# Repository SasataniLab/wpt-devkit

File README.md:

# wpt-devkit-v0.1 SCPI Command Set
Hardware tool and Arduino library for developing wireless power applications.

## Command reference
[SCPI command reference](./docs/SCPI.md)

## Arduino IDE
### Installation
Add `wpt-io-arduino.zip` in release.
- Sketch -> Include Library -> Add .ZIP Library

### Dependencies
**Manual ZIP install**
- [bschulz1701/PAC1720_Library](https://github.com/bschulz1701/PAC1720_Library)

**Arduino Library Manager**
- [WifWaf/MCP45HVX1](https://github.com/WifWaf/MCP45HVX1)

### Update
You need to manually uninstall to update. We plan to add this to Arduino Library Manager to automate this in the future.

## Examples
See [Examples](./firmware/wpt-io-arduino/examples) for example Arduino sketches

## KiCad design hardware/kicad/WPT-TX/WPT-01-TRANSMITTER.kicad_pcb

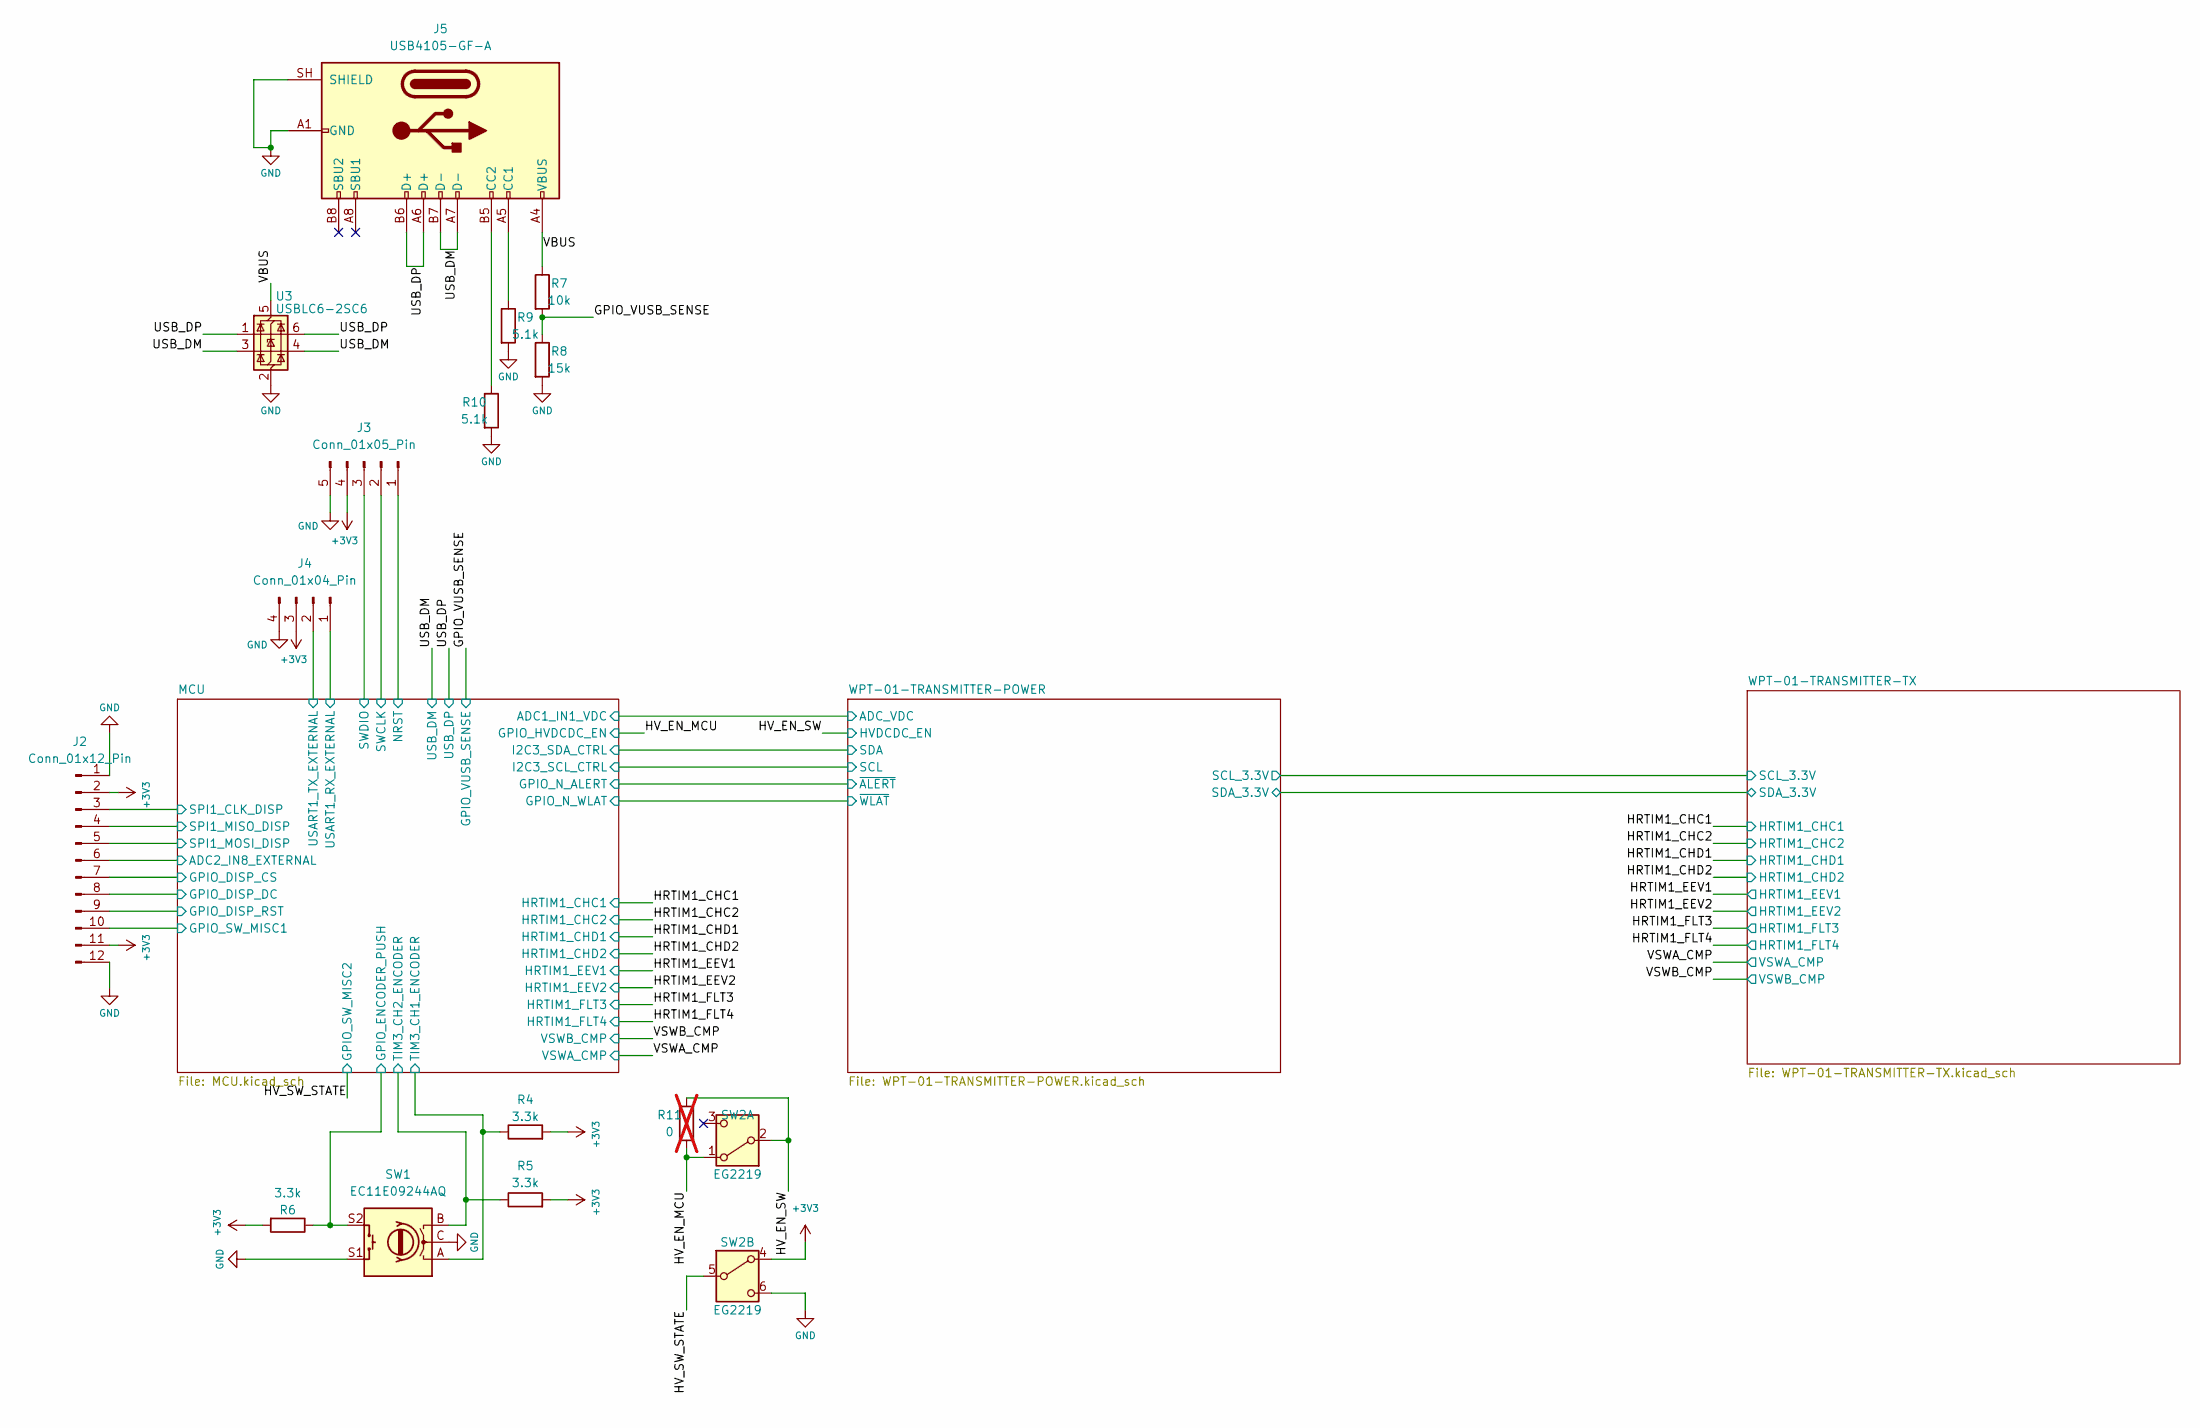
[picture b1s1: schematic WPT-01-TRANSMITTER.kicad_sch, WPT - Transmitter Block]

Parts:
J2: Conn_01x12_Pin; PinHeader_1x12_P2.54mm_Vertical
J3: Conn_01x05_Pin; PinHeader_1x05_P2.54mm_Vertical
J4: Conn_01x04_Pin; PinHeader_1x04_P2.54mm_Vertical
J5: USB4105-GF-A; USB_C_Receptacle_GCT_USB4105-xx-A_16P_TopMnt_Horizontal
R4, R5, R6: 3.3k; R_0402_1005Metric
R7: 10k; R_0402_1005Metric
R8: 15k; R_0402_1005Metric
R9, R10: 5.1k; R_0402_1005Metric
R11: 0; R_0402_1005Metric; not fitted
SW1: EC11E09244AQ; RotaryEncoder_Alps_EC11E-Switch_Vertical_H20mm
SW2: EG2219; SW_E-Switch_EG2219_DPDT_Angled
U3: USBLC6-2SC6; SOT-23-6

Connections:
+3V3: J2.2, J2.11, J3.4, J4.3, R4.2, R5.2, R6.2, SW2.4 (A); also elsewhere on the board
/GPIO_VUSB_SENSE: R7.2, R8.1; also elsewhere on the board
/HV_EN_MCU: R11.2, SW2.1 (A); also elsewhere on the board
/HV_EN_SW: R11.1, SW2.2 (B); also elsewhere on the board
/HV_SW_STATE: SW2.5 (B); also elsewhere on the board
/MCU/ADC2_IN8_EXTERNAL: J2.6; also elsewhere on the board
/MCU/GPIO_DISP_CS: J2.7; also elsewhere on the board
/MCU/GPIO_DISP_DC: J2.8; also elsewhere on the board
/MCU/GPIO_DISP_RST: J2.9; also elsewhere on the board
/MCU/GPIO_ENCODER_PUSH: R6.1, SW1.S2; also elsewhere on the board
/MCU/GPIO_SW_MISC1: J2.10; also elsewhere on the board
/MCU/NRST: J3.1; also elsewhere on the board
/MCU/SPI1_CLK_DISP: J2.3; also elsewhere on the board
/MCU/SPI1_MISO_DISP: J2.4; also elsewhere on the board
/MCU/SPI1_MOSI_DISP: J2.5; also elsewhere on the board
/MCU/SWCLK: J3.2; also elsewhere on the board
/MCU/SWDIO: J3.3; also elsewhere on the board
/MCU/TIM3_CH1_ENCODER: R4.1, SW1.A; also elsewhere on the board
/MCU/TIM3_CH2_ENCODER: R5.1, SW1.B; also elsewhere on the board
/MCU/USART1_RX_EXTERNAL: J4.1; also elsewhere on the board
/MCU/USART1_TX_EXTERNAL: J4.2; also elsewhere on the board
/USB_DM: J5.A7 (D-), J5.B7 (D-), U3.3 (I/O2), U3.4 (I/O2); also elsewhere on the board
/USB_DP: J5.A6 (D+), J5.B6 (D+), U3.1 (I/O1), U3.6 (I/O1); also elsewhere on the board
/VBUS: J5.A4 (VBUS), J5.A9 (VBUS), J5.B4 (VBUS), J5.B9 (VBUS), R7.1, U3.5 (VBUS)
GND: J2.1, J2.12, J3.5, J4.4, J5.A1 (GND), J5.A12 (GND), J5.B1 (GND), J5.B12 (GND), J5.SH (SHIELD), R8.2, R9.2, R10.2, SW1.C, SW1.S1, SW2.6 (C), U3.2 (GND); also elsewhere on the board
unnamed: J5.A5 (CC1), R9.1
unnamed: J5.B5 (CC2), R10.1

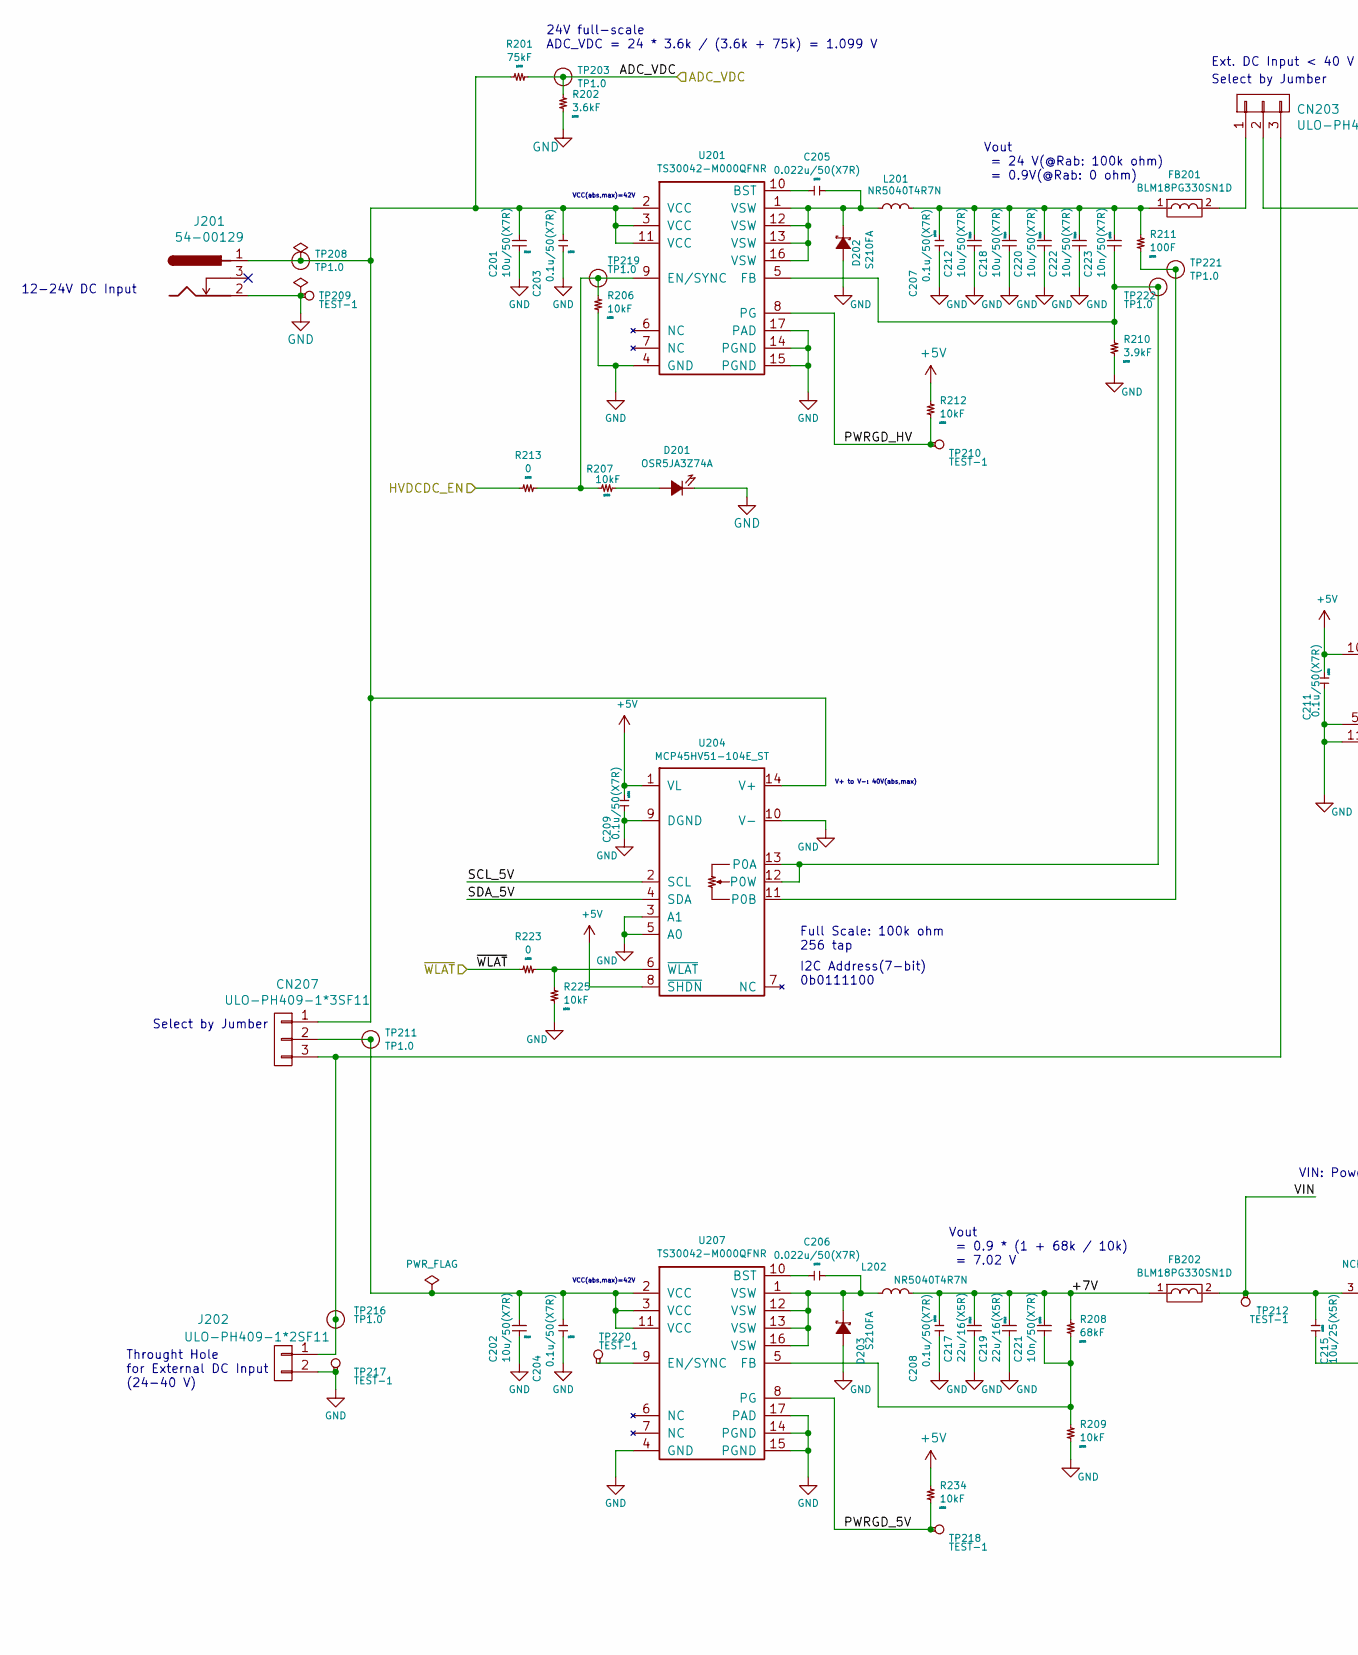
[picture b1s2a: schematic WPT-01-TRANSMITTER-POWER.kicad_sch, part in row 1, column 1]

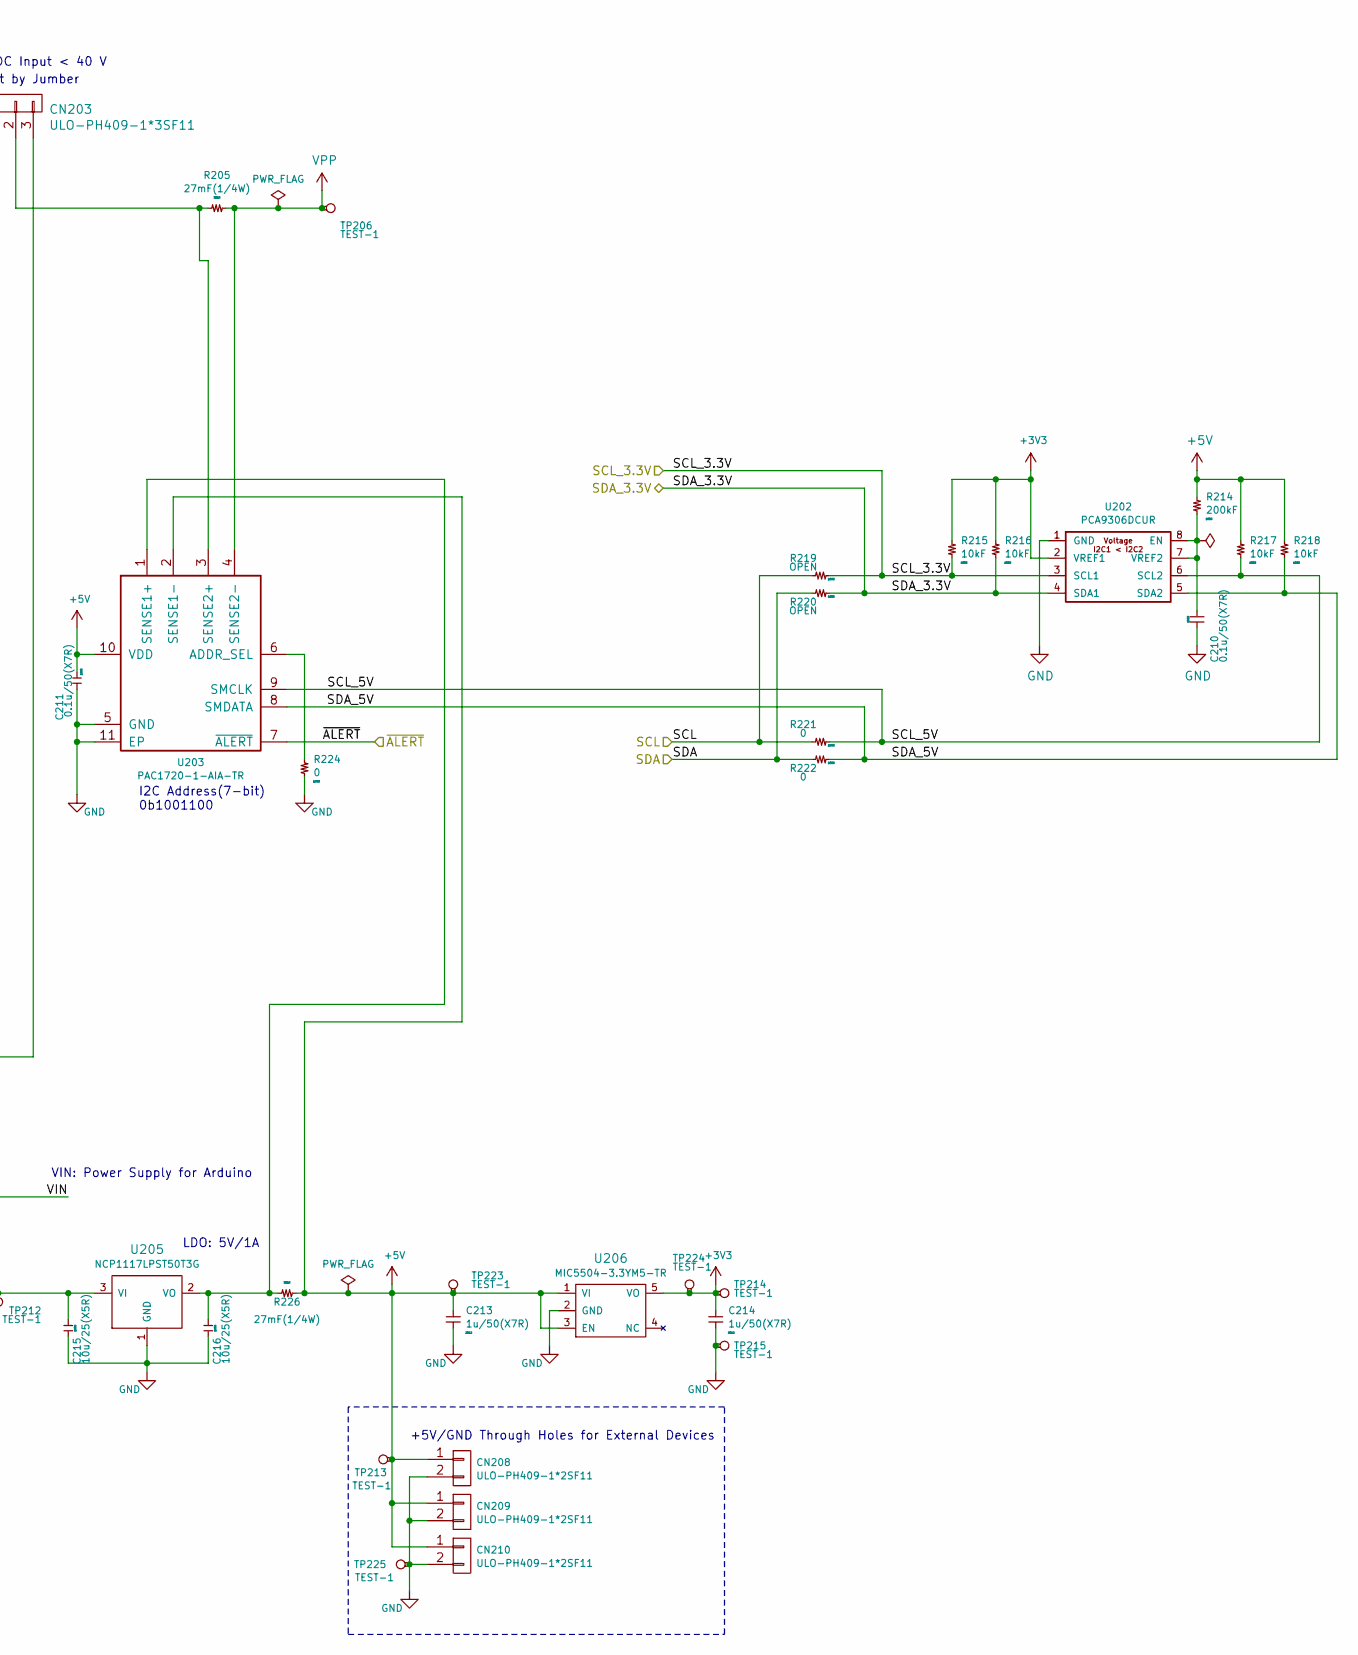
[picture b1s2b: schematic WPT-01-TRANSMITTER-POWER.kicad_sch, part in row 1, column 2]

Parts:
C201, C202, C212, C218, C220, C222: 10u/50(X7R); GRM31; Manufacturer Part Number CL31A106KBHNNNE
C203, C204, C207, C208, C209, C210, C211: 0.1u/50(X7R); GRM15; Manufacturer Part Number GCM155R71H104KE02D
C205, C206: 0.022u/50(X7R); GRM15; Manufacturer Part Number GRM155R71H223KA12D
C213, C214: 1u/50(X7R); GRM21; Manufacturer Part Number CL21B105KBFNNNG
C215, C216: 10u/25(X5R); GRM18; Manufacturer Part Number GRM188R61E106MA73D
C217, C219: 22u/16(X5R); GRM21; Manufacturer Part Number CL21A226MOCLRNC
C221, C223: 10n/50(X7R); GRM15; Manufacturer Part Number CC0402KRX7R9BB103
CN203, CN207: ULO-PH409-1*3SF11; ULO-PH409-1x3SX1; Manufacturer Part Number ULO-PH409-1*3SF11
CN208, CN209, CN210: ULO-PH409-1*2SF11; ULO-PH409-1x2SX1; Manufacturer Part Number ULO-PH409-1x2SX1
D201: OSR5JA3Z74A; LED_D3.0mm; Manufacturer Part Number OSR5JA3Z74A
D202, D203: S210FA; SOD-123FA_OnSemi; Manufacturer Part Number S210FA
FB201, FB202: BLM18PG330SN1D; BLM18; Manufacturer Part Number BLM18PG330SN1D
J201: 54-00129; Manufacturer Part Number 54-00129
J202: ULO-PH409-1*2SF11; ULO-PH409-1x2SX1; Manufacturer Part Number ULO-PH409-1x2SX1
L201: NR5040T4R7N; NR5040
L202: NR5040T4R7N; NR5040; Manufacturer Part Number NR5040T4R7N
R201: 75kF; R_0402; Manufacturer Part Number RC0402FR-0775KL
R202: 3.6kF; R_0402; Manufacturer Part Number RC0402FR-073K6L
R205, R226: 27mF(1/4W); R_1206; Manufacturer Part Number RL1206FR-070R027L
R206, R207, R209, R212, R215, R216, R217, R218, R225, R234: 10kF; R_0402; Manufacturer Part Number RC0402FR-0710KL
R208: 68kF; R_0402; Manufacturer Part Number RC0402FR-0768KL
R210: 3.9kF; R_0402; Manufacturer Part Number RC0402FR-073K9L
R211: 100F; R_0402; Manufacturer Part Number RC0402FR-07100RL
R213, R221, R222, R223, R224: 0; R_0402; Manufacturer Part Number RC0402FR-070RL
R214: 200kF; R_0402; Manufacturer Part Number RC0402FR-07200KL
R219, R220: OPEN; R_0402; Manufacturer Part Number RC0402FR-070RL
TP203, TP208, TP211, TP216, TP219, TP221, TP222: TP1.0; TP_1mm
TP206, TP209, TP210, TP212, TP213, TP214, TP215, TP217, TP218, TP220, TP223, TP224, TP225: TEST-1; PTH_1mm
U201, U207: TS30042-M000QFNR; QFN-16-1EP_3x3mm_Pitch0.5mm_Semtech; Manufacturer Part Number TS30042-M000QFNR
U202: PCA9306DCUR; Texas_S-PDSO-G8; Manufacturer Part Number PCA9306DCUR
U203: PAC1720-1-AIA-TR; DFN-10-1EP_3x3mm_Pitch0.5mm_microchip_9Q; Manufacturer Part Number PAC1720-1-AIA-TR
U204: MCP45HV51-104E_ST; TSSOP-14_4.4x5mm_P0.65mm; Manufacturer Part Number MCP45HV51-104E_ST
U205: NCP1117LPST50T3G; SOT-223-3_TabPin2; Manufacturer Part Number NCP1117LPST50T3G
U206: MIC5504-3.3YM5-TR; microchip_SOT23-5LD-PL-1; Manufacturer Part Number MIC5504-3.3YM5-TR

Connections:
+3V3: C214.1, R215.2, R216.2, TP214.1 (~_1), TP224.1 (~_1), U202.2 (VREF1), U206.5 (VO); also elsewhere on the board
+5V: C209.2, C211.2, C213.1, CN208.1, CN209.1, CN210.1, R212.2, R214.2, R217.2, R218.2, R226.1, R234.2, TP213.1 (~_1), TP223.1 (~_1), U203.2 (SENSE1-), U203.10 (VDD), U204.1 (VL), U204.8 (~SHDN), U206.1 (VI), U206.3 (EN); also elsewhere on the board
/HV_EN_SW: R213.2; also elsewhere on the board
/WPT-01-TRANSMITTER-POWER/+7V: C208.1, C217.1, C219.1, C221.1, FB202.1, L202.2, R208.2
/WPT-01-TRANSMITTER-POWER/ADC_VDC: R201.1, R202.2, TP203.1 (~_1); also elsewhere on the board
/WPT-01-TRANSMITTER-POWER/PWRGD_5V: R234.1, TP218.1 (~_1), U207.8 (PG)
/WPT-01-TRANSMITTER-POWER/PWRGD_HV: R212.1, TP210.1 (~_1), U201.8 (PG)
/WPT-01-TRANSMITTER-POWER/SCL: R219.2, R221.2; also elsewhere on the board
/WPT-01-TRANSMITTER-POWER/SCL_3.3V: R215.1, R219.1, U202.3 (SCL1); also elsewhere on the board
/WPT-01-TRANSMITTER-POWER/SCL_5V: R217.1, R221.1, U202.6 (SCL2), U203.9 (SMCLK), U204.2 (SCL)
/WPT-01-TRANSMITTER-POWER/SDA: R220.2, R222.2; also elsewhere on the board
/WPT-01-TRANSMITTER-POWER/SDA_3.3V: R216.1, R220.1, U202.4 (SDA1); also elsewhere on the board
/WPT-01-TRANSMITTER-POWER/SDA_5V: R218.1, R222.1, U202.5 (SDA2), U203.8 (SMDATA), U204.4 (SDA)
/WPT-01-TRANSMITTER-POWER/VIN: C215.1, FB202.2, TP212.1 (~_1), U205.3 (VI)
/WPT-01-TRANSMITTER-POWER/~ALERT: U203.7 (~ALERT); also elsewhere on the board
/WPT-01-TRANSMITTER-POWER/~WLAT: R223.2; also elsewhere on the board
GND: C201.2, C202.2, C203.2, C204.2, C207.2, C208.2, C209.1, C210.2, C211.1, C212.2, C213.2, C214.2, C215.2, C216.2, C217.2, C218.2, C219.2, C220.2, C222.2, CN208.2, CN209.2, CN210.2, D201.1 (K), D202.2 (A), D203.2 (A), J201.2, J202.2, R202.1, R206.1, R209.1, R210.1, R224.1, R225.1, TP209.1 (~_1), TP215.1 (~_1), TP217.1 (~_1), TP225.1 (~_1), U201.4 (GND), U201.14 (PGND), U201.15 (PGND), U201.17 (PAD), U202.1 (GND), U203.5 (GND), U203.11 (EP), U204.3 (A1), U204.5 (A0), U204.9 (DGND), U204.10 (V-), U205.1 (GND), U206.2 (GND), U207.4 (GND), U207.14 (PGND), U207.15 (PGND), U207.17 (PAD); also elsewhere on the board
unnamed: C207.1, C212.1, C218.1, C220.1, C222.1, C223.1, FB201.1, L201.2, R211.2
unnamed: CN203.1, FB201.2
unnamed: CN203.2, R205.2, U203.3 (SENSE2+)
unnamed: CN203.3, CN207.3, J202.1, TP216.1 (~_1)
unnamed: C201.1, C203.1, CN207.1, J201.1, R201.2, TP208.1 (~_1), U201.2 (VCC), U201.3 (VCC), U201.11 (VCC), U204.14 (V+)
unnamed: C202.1, C204.1, CN207.2, TP211.1 (~_1), U207.2 (VCC), U207.3 (VCC), U207.11 (VCC)
unnamed: D201.2 (A), R207.2
unnamed: C205.2, D202.1 (K), L201.1, U201.1 (VSW), U201.12 (VSW), U201.13 (VSW), U201.16 (VSW)
unnamed: C206.2, D203.1 (K), L202.1, U207.1 (VSW), U207.12 (VSW), U207.13 (VSW), U207.16 (VSW)
unnamed: R206.2, R207.1, R213.1, TP219.1 (~_1), U201.9 (EN/SYNC)
unnamed: TP220.1 (~_1), U207.9 (EN/SYNC)
unnamed: R211.1, TP221.1 (~_1), U204.11 (P0B)
unnamed: C223.2, R210.2, TP222.1 (~_1), U201.5 (FB), U204.12 (P0W), U204.13 (P0A)
unnamed: C205.1, U201.10 (BST)
unnamed: C210.1, R214.1, U202.7 (VREF2), U202.8 (EN)
unnamed: R224.2, U203.6 (ADDR_SEL)
unnamed: C216.1, R226.2, U203.1 (SENSE1+), U205.2 (VO)
unnamed: R223.1, R225.2, U204.6 (~WLAT)
unnamed: C206.1, U207.10 (BST)
unnamed: C221.2, R208.1, R209.2, U207.5 (FB)
VPP: R205.1, TP206.1 (~_1), U203.4 (SENSE2-); also elsewhere on the board

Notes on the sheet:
Throught Hole for External DC Input (24-40 V)
Vout = 24 V(@Rab: 100k ohm) = 0.9V(@Rab: 0 ohm)
24V full-scale ADC_VDC = 24 * 3.6k / (3.6k + 75k) = 1.099 V
Full Scale: 100k ohm 256 tap
VCC(abs,max)=42V
12-24V DC Input
Vout = 0.9 * (1 + 68k / 10k) = 7.02 V
LDO: 5V/1A
Ext. DC Input < 40 V
VIN: Power Supply for Arduino
I2C Address(7-bit) 0b1001100
V+ to V-: 40V(abs,max)
Select by Jumber
+5V/GND Through Holes for External Devices
I2C Address(7-bit) 0b0111100

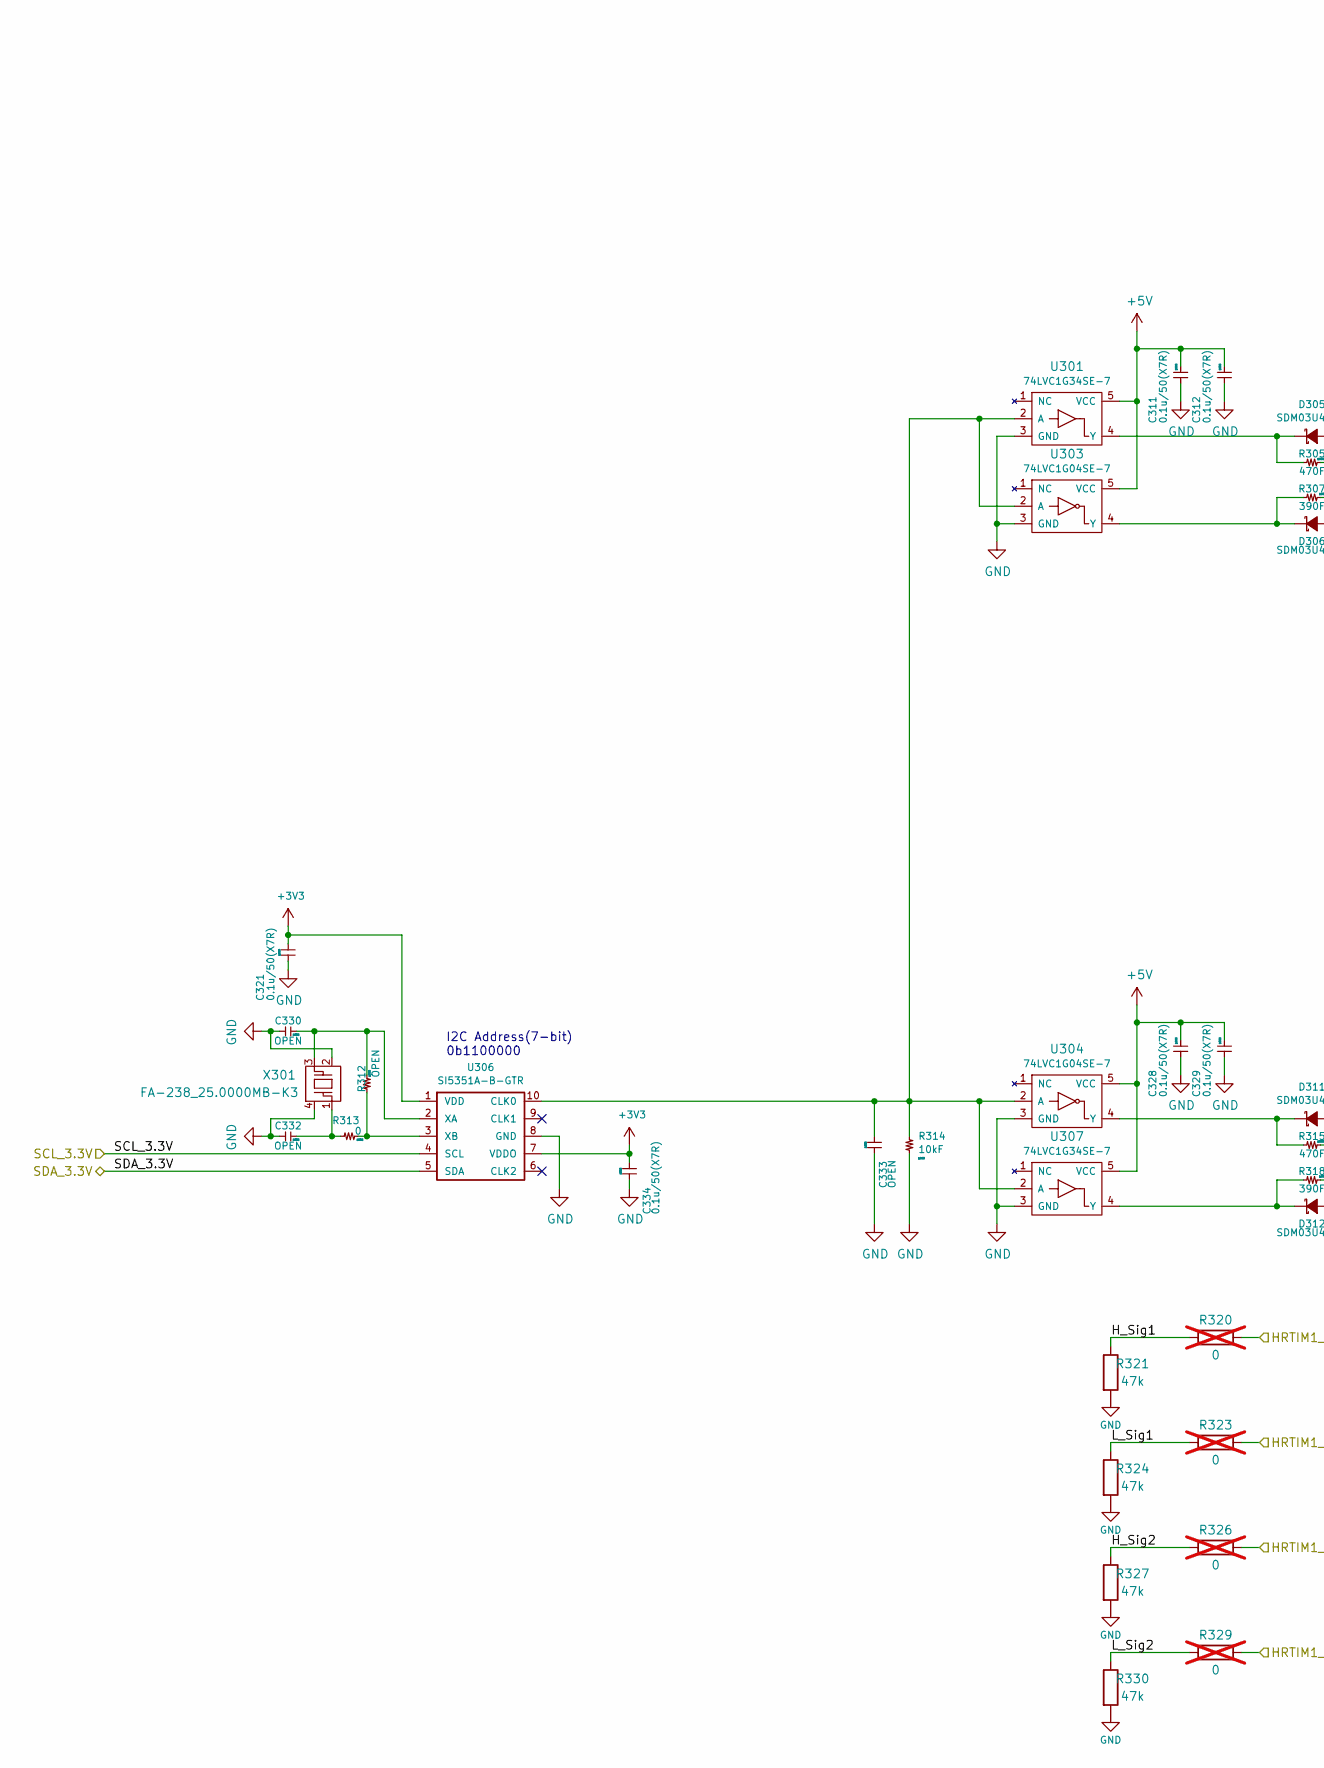
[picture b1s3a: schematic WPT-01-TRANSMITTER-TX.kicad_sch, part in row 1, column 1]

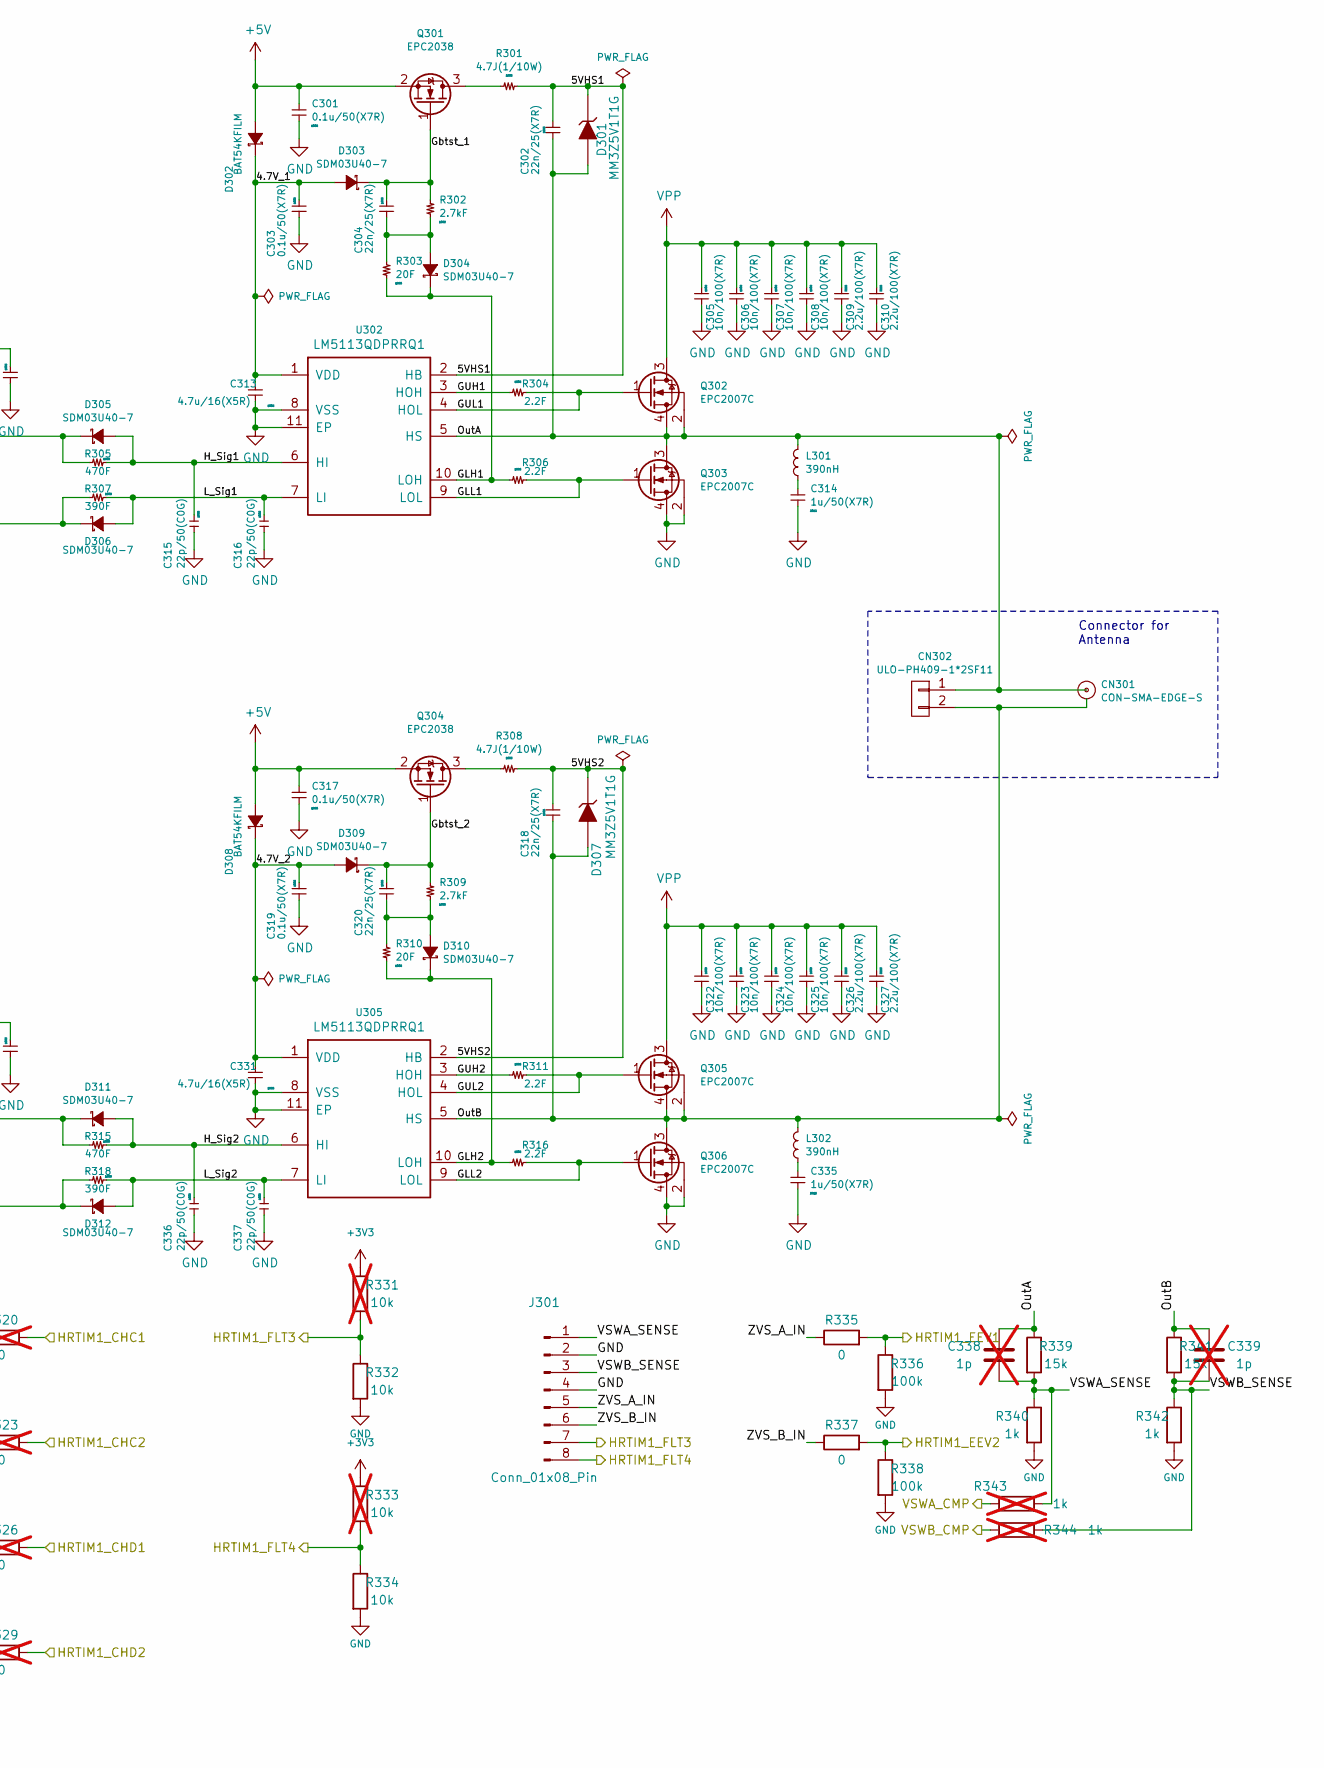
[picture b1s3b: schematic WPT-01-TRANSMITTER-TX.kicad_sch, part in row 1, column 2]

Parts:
C301, C303, C311, C312, C317, C319, C321, C328, C329, C334: 0.1u/50(X7R); GRM15; Manufacturer Part Number GCM155R71H104KE02D
C302, C304, C318, C320: 22n/25(X7R); GRM15; Manufacturer Part Number CC0402KRX7R8BB223
C305, C306, C307, C308, C322, C323, C324, C325: 10n/100(X7R); GRM18; Manufacturer Part Number CL10B103KC8WPNC
C309, C310, C326, C327: 2.2u/100(X7R); GRM32; Manufacturer Part Number CL32B225KCJZW6E
C313, C331: 4.7u/16(X5R); GRM15; Manufacturer Part Number CL05A475MO5NUNC
C314, C335: 1u/50(X7R); GRM21; Manufacturer Part Number CL21B105KBFNNNG
C315, C316, C336, C337: 22p/50(C0G); GRM15; Manufacturer Part Number GCM1555C1H220JA16D
C330, C332: OPEN; GRM15; Manufacturer Part Number GRM15
C333: OPEN; GRM15; Manufacturer Part Number CC0402
C338, C339: 1p; C_0402_1005Metric; not fitted
CN301: CON-SMA-EDGE-S; Manufacturer Part Number CON-SMA-EDGE-S
CN302: ULO-PH409-1*2SF11; ULO-PH409-1x2SX1; Manufacturer Part Number ULO-PH409-1x2SX1
D301, D307: MM3Z5V1T1G; SOD-323; Manufacturer Part Number MM3Z5V1T1G
D302, D308: BAT54KFILM; SOD-523F_STMicroelectronics; Manufacturer Part Number BAT54KFILM
D303, D304, D305, D306, D309, D310, D311, D312: SDM03U40-7; SOD-523F_Diodes; Manufacturer Part Number SDM03U40-7
J301: Conn_01x08_Pin; PinHeader_1x08_P2.54mm_Vertical
L301, L302: 390nH; 2929SQ; Manufacturer Part Number 2929SQ-391JEB
Q301, Q304: EPC2038; Manufacturer Part Number EPC2038
Q302, Q303, Q305, Q306: EPC2007C; Manufacturer Part Number EPC2007C
R301, R308: 4.7J(1/10W); R_0402; Manufacturer Part Number ERJ-2GEJ4R7X
R302, R309: 2.7kF; R_0402; Manufacturer Part Number RC0402FR-072K7L
R303, R310: 20F; R_0402; Manufacturer Part Number RC0402FR-0720RL
R304, R306, R311, R316: 2.2F; R_0402; Manufacturer Part Number RC0402FR-072R2L
R305, R315: 470F; R_0603; Manufacturer Part Number RC0603FR-07470RL
R307, R318: 390F; R_0603; Manufacturer Part Number RC0603FR-07390RL
R312: OPEN; R_0402; Manufacturer Part Number RC0402
R313: 0; R_0402; Manufacturer Part Number RC0402FR-070RL
R314: 10kF; R_0402; Manufacturer Part Number RC0402FR-0710KL
R320, R323, R326, R329: 0; R_0402_1005Metric; not fitted
R321, R324, R327, R330: 47k; R_0402_1005Metric
R331, R333: 10k; R_0402_1005Metric; not fitted
R332, R334: 10k; R_0402_1005Metric
R335, R337: 0; R_0402_1005Metric
R336, R338: 100k; R_0402_1005Metric
R339, R341: 15k; R_0402_1005Metric
R340, R342: 1k; R_0402_1005Metric
R343, R344: 1k; R_0402_1005Metric; not fitted
U301, U307: 74LVC1G34SE-7; SOT-353_SC-70-5_Diodes; Manufacturer Part Number 74LVC1G34SE-7
U302, U305: LM5113QDPRRQ1; Texas_S-PWSON-N10_ThermalVias; Manufacturer Part Number LM5113QDPRRQ1
U303, U304: 74LVC1G04SE-7; SOT-353_SC-70-5_Diodes; Manufacturer Part Number 74LVC1G04SE-7
U306: SI5351A-B-GTR; Siliconlabs_MSOP-10_3x3mm_Pitch0.5mm; Manufacturer Part Number SI5351A-B-GTR
X301: FA-238_25.0000MB-K3; FA-238; Manufacturer Part Number FA-238_25.0000MB-K3

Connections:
+3V3: C321.1, C334.1, R331.1, R333.1, U306.1 (VDD), U306.7 (VDDO); also elsewhere on the board
+5V: C301.1, C311.1, C312.1, C317.1, C328.1, C329.1, D302.2 (A), D308.2 (A), Q301.2 (S), Q304.2 (S), U301.5 (VCC), U303.5 (VCC), U304.5 (VCC), U307.5 (VCC); also elsewhere on the board
/HRTIM1_CHC1: R320.2; also elsewhere on the board
/HRTIM1_CHC2: R323.2; also elsewhere on the board
/HRTIM1_CHD1: R326.2; also elsewhere on the board
/HRTIM1_CHD2: R329.2; also elsewhere on the board
/HRTIM1_EEV1: R335.2, R336.1; also elsewhere on the board
/HRTIM1_EEV2: R337.2, R338.1; also elsewhere on the board
/HRTIM1_FLT3: J301.7, R331.2, R332.1; also elsewhere on the board
/HRTIM1_FLT4: J301.8, R333.2, R334.1; also elsewhere on the board
/VSWA_CMP: R343.1; also elsewhere on the board
/VSWB_CMP: R344.1; also elsewhere on the board
/WPT-01-TRANSMITTER-POWER/SCL_3.3V: U306.4 (SCL); also elsewhere on the board
/WPT-01-TRANSMITTER-POWER/SDA_3.3V: U306.5 (SDA); also elsewhere on the board
/WPT-01-TRANSMITTER-TX/4.7V_1: C303.1, C313.1, D302.1 (C), D303.2 (A), U302.1 (VDD)
/WPT-01-TRANSMITTER-TX/4.7V_2: C319.1, C331.1, D308.1 (C), D309.2 (A), U305.1 (VDD)
/WPT-01-TRANSMITTER-TX/5VHS1: C302.1, D301.1 (K), R301.1, U302.2 (HB)
/WPT-01-TRANSMITTER-TX/5VHS2: C318.1, D307.1 (K), R308.1, U305.2 (HB)
/WPT-01-TRANSMITTER-TX/GLH1: D304.1 (C), R303.1, R306.2, U302.10 (LOH)
/WPT-01-TRANSMITTER-TX/GLH2: D310.1 (C), R310.1, R316.2, U305.10 (LOH)
/WPT-01-TRANSMITTER-TX/GLL1: Q303.1 (G), R306.1, U302.9 (LOL)
/WPT-01-TRANSMITTER-TX/GLL2: Q306.1 (G), R316.1, U305.9 (LOL)
/WPT-01-TRANSMITTER-TX/GUH1: R304.2, U302.3 (HOH)
/WPT-01-TRANSMITTER-TX/GUH2: R311.2, U305.3 (HOH)
/WPT-01-TRANSMITTER-TX/GUL1: Q302.1 (G), R304.1, U302.4 (HOL)
/WPT-01-TRANSMITTER-TX/GUL2: Q305.1 (G), R311.1, U305.4 (HOL)
/WPT-01-TRANSMITTER-TX/Gbtst_1: C304.1, D303.1 (C), Q301.1 (G), R302.2
/WPT-01-TRANSMITTER-TX/Gbtst_2: C320.1, D309.1 (C), Q304.1 (G), R309.2
/WPT-01-TRANSMITTER-TX/H_Sig1: C315.1, D305.2 (A), R305.1, R320.1, R321.1, U302.6 (HI)
/WPT-01-TRANSMITTER-TX/H_Sig2: C336.1, D311.2 (A), R315.1, R326.1, R327.1, U305.6 (HI)
/WPT-01-TRANSMITTER-TX/L_Sig1: C316.1, D306.2 (A), R307.1, R323.1, R324.1, U302.7 (LI)
/WPT-01-TRANSMITTER-TX/L_Sig2: C337.1, D312.2 (A), R318.1, R329.1, R330.1, U305.7 (LI)
/WPT-01-TRANSMITTER-TX/OutA: C302.2, C338.1, CN301.1, CN302.1, D301.2 (A), L301.2, Q302.2 (S), Q302.4 (S), Q303.3 (D), R339.1, U302.5 (HS)
/WPT-01-TRANSMITTER-TX/OutB: C318.2, C339.1, CN301.2, CN302.2, D307.2 (A), L302.2, Q305.2 (S), Q305.4 (S), Q306.3 (D), R341.1, U305.5 (HS)
/WPT-01-TRANSMITTER-TX/VSWA_SENSE: C338.2, J301.1, R339.2, R340.1, R343.2
/WPT-01-TRANSMITTER-TX/VSWB_SENSE: C339.2, J301.3, R341.2, R342.1, R344.2
/WPT-01-TRANSMITTER-TX/ZVS_A_IN: J301.5, R335.1
/WPT-01-TRANSMITTER-TX/ZVS_B_IN: J301.6, R337.1
GND: C301.2, C303.2, C305.2, C306.2, C307.2, C308.2, C309.2, C310.2, C311.2, C312.2, C313.2, C314.2, C315.2, C316.2, C317.2, C319.2, C321.2, C322.2, C323.2, C324.2, C325.2, C326.2, C327.2, C328.2, C329.2, C330.1, C331.2, C332.1, C333.2, C334.2, C335.2, C336.2, C337.2, J301.2, J301.4, Q303.2 (S), Q303.4 (S), Q306.2 (S), Q306.4 (S), R314.1, R321.2, R324.2, R327.2, R330.2, R332.2, R334.2, R336.2, R338.2, R340.2, R342.2, U301.3 (GND), U302.8 (VSS), U302.11 (EP), U303.3 (GND), U304.3 (GND), U305.8 (VSS), U305.11 (EP), U306.8 (GND), U307.3 (GND), X301.2, X301.4; also elsewhere on the board
unnamed: C314.1, L301.1
unnamed: C332.2, R313.2, X301.1
unnamed: C335.1, L302.1
unnamed: C304.2, D304.2 (A), R302.1, R303.2
unnamed: D305.1 (C), R305.2, U301.4 (Y)
unnamed: D306.1 (C), R307.2, U303.4 (Y)
unnamed: C320.2, D310.2 (A), R309.1, R310.2
unnamed: D311.1 (C), R315.2, U304.4 (Y)
unnamed: D312.1 (C), R318.2, U307.4 (Y)
unnamed: Q301.3 (D), R301.2
unnamed: Q304.3 (D), R308.2
unnamed: C333.1, R314.2, U301.2 (A), U303.2 (A), U304.2 (A), U306.10 (CLK0), U307.2 (A)
unnamed: C330.2, R312.2, U306.2 (XA), X301.3
unnamed: R312.1, R313.1, U306.3 (XB)
VPP: C305.1, C306.1, C307.1, C308.1, C309.1, C310.1, C322.1, C323.1, C324.1, C325.1, C326.1, C327.1, Q302.3 (D), Q305.3 (D); also elsewhere on the board

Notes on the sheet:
Connector for Antenna
I2C Address(7-bit) 0b1100000
